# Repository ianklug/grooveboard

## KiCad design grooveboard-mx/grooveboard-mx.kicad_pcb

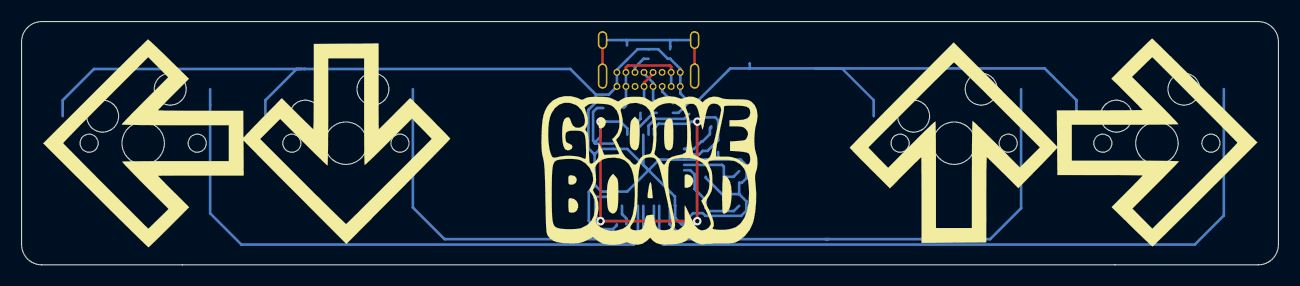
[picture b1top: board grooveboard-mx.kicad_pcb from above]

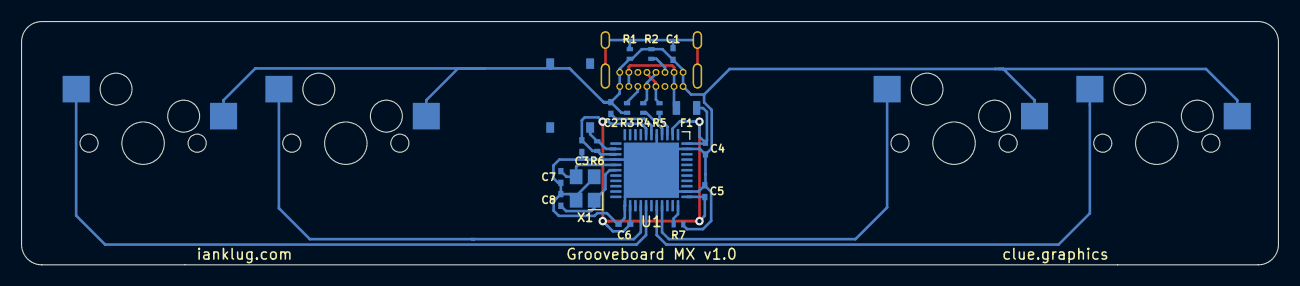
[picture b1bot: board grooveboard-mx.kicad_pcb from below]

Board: 2 copper layers, 118.1 x 22.9 mm, 24 parts (19 on the bottom side), 19 nets.

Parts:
C1: 4.7nF; C_0402
C2: 1uF; C_0402
C3, C4, C5: 0.1uF; C_0402
C6: 10uF; C_0402
C7, C8: 22pF; C_0402
F1: 500mA; Fuse_0805
J1: USB_C_Receptacle_USB2.0; USB_C_GCT_USB4085
MX1, MX2, MX3, MX4: MX-NoLED; Kailh_socket_MX
R1: 1M; R_0402
R2, R3: 5.1k; R_0402
R4, R5: 22; R_0402
R6, R7: 10k; R_0402
SW1: SW_Push; TS-1187A-B-A-B
U1: ATmega32U4-MU; QFN-44-1EP_7x7mm_P0.5mm_EP5.2x5.2mm
X1: 16MHz; Crystal_SMD_3225-4pin_3.2x2.5mm

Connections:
D+: R4.1, U1.4
D-: R5.1, U1.3
GND: C1.2, C2.2, C3.2, C4.2, C5.2, C6.2, C7.1, C8.1, J1.A1, J1.A12, J1.B1, J1.B12, MX1.2, MX2.2, MX3.2, MX4.2, R1.2, R2.1, R3.1, R7.1, SW1.1, U1.5, U1.15, U1.23, U1.35, U1.43, U1.45, X1.2, X1.4
MX1: MX1.1, U1.29
MX2: MX2.1, U1.30
MX3: MX3.1, U1.26
MX4: MX4.1, U1.27
unnamed: C1.1, J1.S1, R1.1
unnamed: C2.1, U1.6
unnamed: C7.2, U1.16, X1.3
unnamed: C8.2, U1.17, X1.1
unnamed: F1.2, J1.A4, J1.A9, J1.B4, J1.B9
unnamed: J1.A5, R3.2
unnamed: J1.A6, J1.B6, R4.2
unnamed: J1.A7, J1.B7, R5.2
unnamed: J1.B5, R2.2
unnamed: R7.2, U1.33
RST: R6.2, SW1.2, U1.13
VCC: C3.1, C4.1, C5.1, C6.1, F1.1, R6.1, U1.2, U1.7, U1.14, U1.24, U1.34, U1.44

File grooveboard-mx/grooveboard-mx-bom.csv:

Comment,Designator,Footprint,LCSC Part Number
4.7nF,C1,402,C1538
1uF,C2,402,C52923
100nF,"C3, C4, C5",402,C1525
10uF,C6,402,C15525
22pF,"C7, C8",402,C1555 
1M,R1,402,C26083
5.1k,"R2, R3",402,C25905
22,"R4, R5",402,C25092
10k,"R6, R7",402,C25744
500mA,F1,805,C261942 
ATmega32U4-MU,U1,QFN-44_EP_7.0x7.0x0.5P ,C45874
TS-1187A-B-A-B,SW1,SMD-SW-4_5.1x5.1x1.5 ,C318884 
16MHz,X1,SMD-3225_4P ,C13738
